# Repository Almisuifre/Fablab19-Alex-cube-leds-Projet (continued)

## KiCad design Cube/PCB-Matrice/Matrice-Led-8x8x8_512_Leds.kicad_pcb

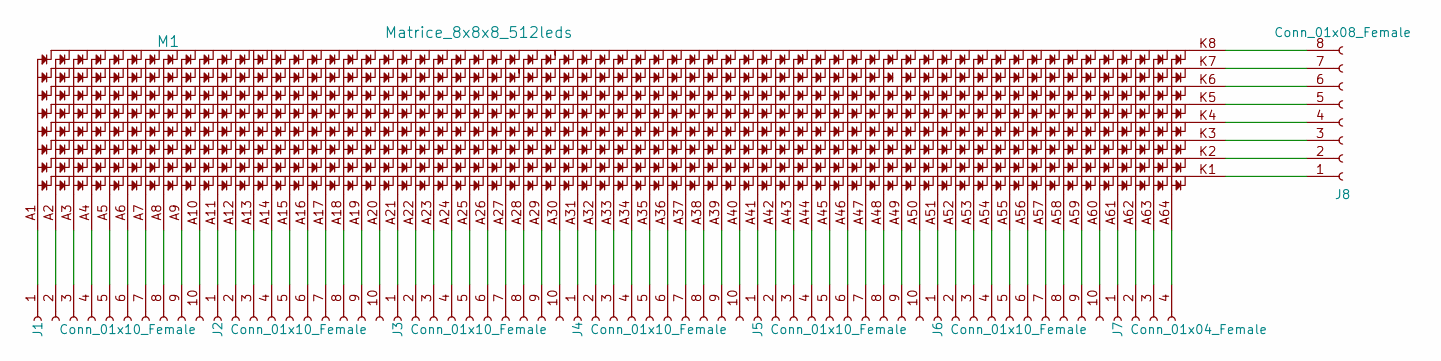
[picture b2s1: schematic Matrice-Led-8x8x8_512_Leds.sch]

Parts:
J1, J2, J3, J4, J5, J6: Conn_01x10_Female; Connect-10pin
J7: Conn_01x04_Female; Connect-4pin
J8: Conn_01x08_Female; Connect-8pin
M1: Matrice_8x8x8_512leds; Matrice-led-8x8x8_512-Leds

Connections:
unnamed: J1.1, M1.A1
unnamed: J1.2, M1.A2
unnamed: J1.3, M1.A3
unnamed: J1.4, M1.A4
unnamed: J1.5, M1.A5
unnamed: J1.6, M1.A6
unnamed: J1.7, M1.A7
unnamed: J1.8, M1.A8
unnamed: J1.9, M1.A9
unnamed: J1.10, M1.A10
unnamed: J2.1, M1.A11
unnamed: J2.2, M1.A12
unnamed: J2.3, M1.A13
unnamed: J2.4, M1.A14
unnamed: J2.5, M1.A15
unnamed: J2.6, M1.A16
unnamed: J2.7, M1.A17
unnamed: J2.8, M1.A18
unnamed: J2.9, M1.A19
unnamed: J2.10, M1.A20
unnamed: J3.1, M1.A21
unnamed: J3.2, M1.A22
unnamed: J3.3, M1.A23
unnamed: J3.4, M1.A24
unnamed: J3.5, M1.A25
unnamed: J3.6, M1.A26
unnamed: J3.7, M1.A27
unnamed: J3.8, M1.A28
unnamed: J3.9, M1.A29
unnamed: J3.10, M1.A30
unnamed: J4.1, M1.A31
unnamed: J4.2, M1.A32
unnamed: J4.3, M1.A33
unnamed: J4.4, M1.A34
unnamed: J4.5, M1.A35
unnamed: J4.6, M1.A36
unnamed: J4.7, M1.A37
unnamed: J4.8, M1.A38
unnamed: J4.9, M1.A39
unnamed: J4.10, M1.A40
unnamed: J5.1, M1.A41
unnamed: J5.2, M1.A42
unnamed: J5.3, M1.A43
unnamed: J5.4, M1.A44
unnamed: J5.5, M1.A45
unnamed: J5.6, M1.A46
unnamed: J5.7, M1.A47
unnamed: J5.8, M1.A48
unnamed: J5.9, M1.A49
unnamed: J5.10, M1.A50
unnamed: J6.1, M1.A51
unnamed: J6.2, M1.A52
unnamed: J6.3, M1.A53
unnamed: J6.4, M1.A54
unnamed: J6.5, M1.A55
unnamed: J6.6, M1.A56
unnamed: J6.7, M1.A57
unnamed: J6.8, M1.A58
unnamed: J6.9, M1.A59
unnamed: J6.10, M1.A60
unnamed: J7.1, M1.A61
unnamed: J7.2, M1.A62
unnamed: J7.3, M1.A63
unnamed: J7.4, M1.A64
unnamed: J8.1, M1.K1
unnamed: J8.2, M1.K2
unnamed: J8.3, M1.K3
unnamed: J8.4, M1.K4
unnamed: J8.5, M1.K5
unnamed: J8.6, M1.K6
unnamed: J8.7, M1.K7
unnamed: J8.8, M1.K8

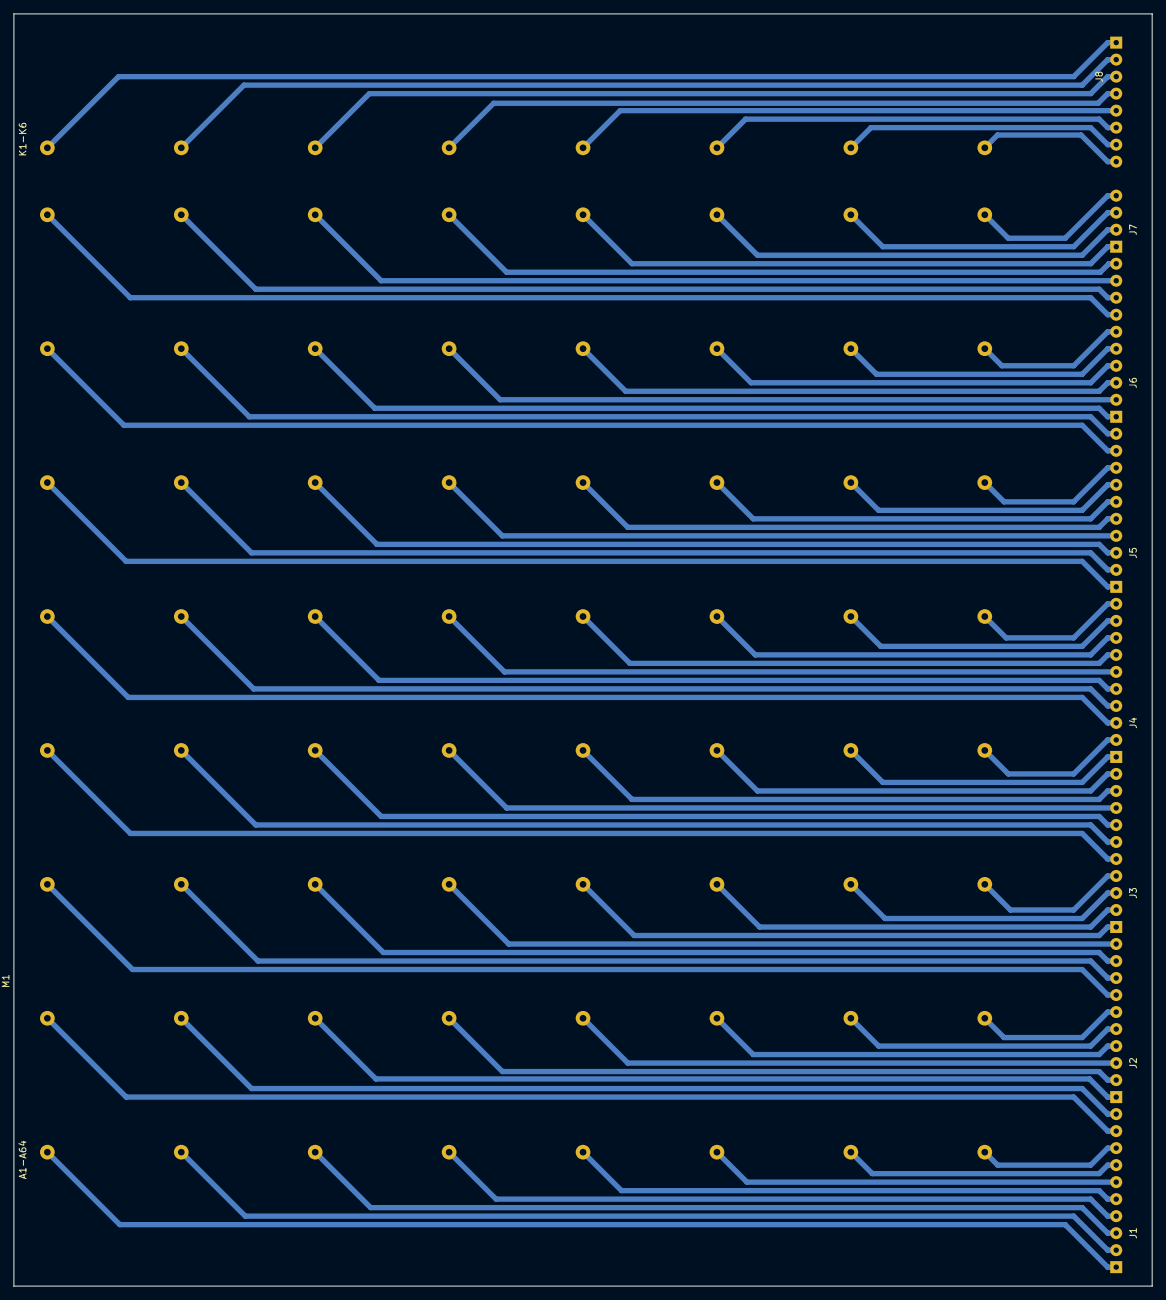
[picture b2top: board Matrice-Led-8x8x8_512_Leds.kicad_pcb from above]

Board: 2 copper layers, 170.0 x 190.0 mm, 9 parts (0 on the bottom side), 72 nets.

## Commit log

2018-05-22 Update
    Update
2018-05-31 Move to old schematic and datasheet
    Move to old schematic and datasheet
    Start New version of project
2018-06-12 Update
    Update Shematic.
    New block Layer.
    Modifynumber block Row.
2018-06-13 Remove Schematic
    Remove Kicad Schematic. New orientation of project !
2018-06-13 Start new project
    Start of a new project
2018-06-20 Update project
    Remove a image corrupted -_-
2018-06-21 Update project
    Update
2018-07-18 Update Project
    Update Project
2018-08-15 Update
    Update
    Add New restistor in Base Q1, Q2, Q3, Q4, Q5, Q6, Q7, Q8
    New version PCB
    New rename components
